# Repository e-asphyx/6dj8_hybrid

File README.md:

# DC coupled hybrid headphone amplifier
The input stage was inspired by Cavalli’s SOHA-II, but I have choose different output design. I use source follower loaded to Norton level shifter fed by op amp DC servo (inspired by TI’s LME49600 reference design) via current mirror to drive simple MOSFET source follower with SSC.

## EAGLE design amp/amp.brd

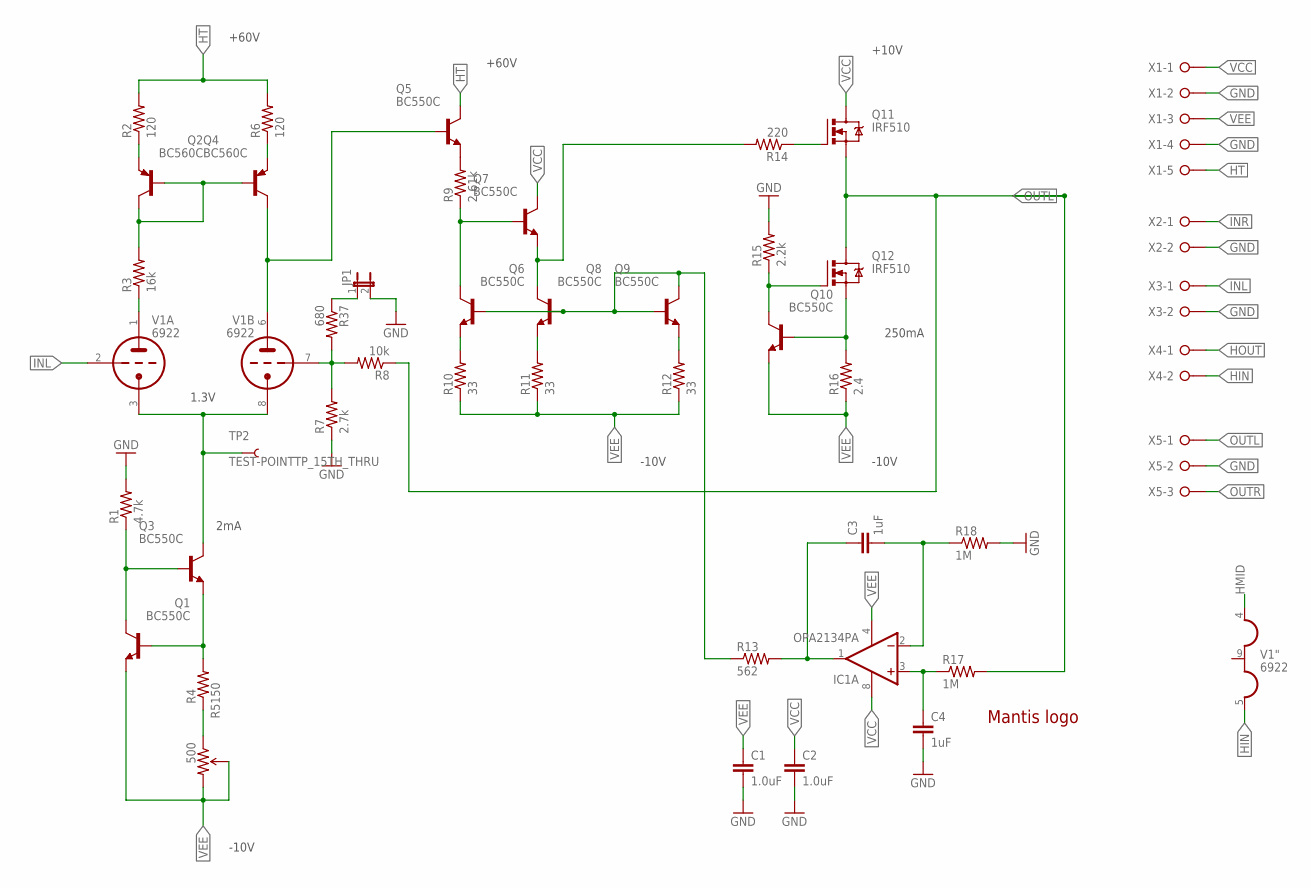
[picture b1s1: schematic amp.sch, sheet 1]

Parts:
C1, C2: 1.0uF; 0805-CAP
C3, C4: 1uF; C5B5
IC1: OPA2134PA; DIL08
JP1: JUMPER-2PTH; 1X02
LOGO1: LOGO-MANTIS
Q1, Q3, Q5, Q6, Q7, Q8, Q9, Q10: BC550C; TO92
Q2, Q4: BC560C; TO92-BENT
Q11, Q12: IRF510; TO220BV
R1: 4.7k; AXIAL-0.4
R2, R6: 120; AXIAL-0.4
R3: 16k; AXIAL-0.4
R4: 150; AXIAL-0.4
R5: 500; 3362U-2
R7: 2.7k; AXIAL-0.4
R8: 10k; AXIAL-0.4
R9: 2.61k; AXIAL-0.4
R10, R11, R12: 33; AXIAL-0.4
R13: 562; AXIAL-0.4
R14: 220; AXIAL-0.4
R15: 2.2k; AXIAL-0.4
R16: 2.4; AXIAL-0.5
R17, R18: 1M; AXIAL-0.4
R37: 680; AXIAL-0.4
TP2: TEST-POINTTP_15TH_THRU; TP_15TH
V1: 6922; NOVAL
X1: W237-05P; W237-5P
X2, X3, X4: W237-02P; W237-132
X5: W237-3E

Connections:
GND: C1.2, C2.2, C4.2, JP1.2, R1.P$2 (2), R7.P$1 (1), R15.P$2 (2), R18.P$2 (2), X1.2, X1.4, X2.2, X3.2, X5.2; also elsewhere on the board
HIN: V1.5 (H3), X4.2
HMID: V1.4 (H1); also elsewhere on the board
HOUT: X4.1; also elsewhere on the board
HT: Q5.3 (C), R2.P$2 (2), R6.P$2 (2), X1.5; also elsewhere on the board
INL: V1.2 (TG), X3.1
INR: X2.1; also elsewhere on the board
unnamed: Q3.3 (C), TP2.P$1, V1.3 (TK), V1.8 (TK)
unnamed: Q2.1 (C), Q2.2 (B), Q4.2 (B), R3.P$2 (2)
unnamed: Q2.3 (E), R2.P$1 (1)
unnamed: Q4.1 (C), Q5.2 (B), V1.6 (TA)
unnamed: R3.P$1 (1), V1.1 (TA)
unnamed: Q4.3 (E), R6.P$1 (1)
unnamed: Q1.2 (B), Q3.1 (E), R4.P$2 (2)
unnamed: Q1.3 (C), Q3.2 (B), R1.P$1 (1)
unnamed: R7.P$2 (2), R8.P$2 (2), R37.P$2 (2), V1.7 (TG)
unnamed: Q6.2 (B), Q8.2 (B), Q9.2 (B), Q9.3 (C), R13.P$1 (1)
unnamed: Q6.1 (E), R10.P$2 (2)
unnamed: Q9.1 (E), R12.P$2 (2)
unnamed: Q5.1 (E), R9.P$2 (2)
unnamed: Q10.3 (C), Q12.G, R15.P$1 (1)
unnamed: Q10.2 (B), Q12.S, R16.P$2 (2)
unnamed: C3.2, IC1.2 (-IN), R18.P$1 (1)
unnamed: C4.1, IC1.3 (+IN), R17.P$1 (1)
unnamed: C3.1, IC1.1 (OUT), R13.P$2 (2)
unnamed: Q8.1 (E), R11.P$2 (2)
unnamed: R4.P$1 (1), R5.1 (CCW)
unnamed: Q11.G, R14.P$1 (1)
unnamed: Q6.3 (C), Q7.2 (B), R9.P$1 (1)
unnamed: Q7.1 (E), Q8.3 (C), R14.P$2 (2)
unnamed: JP1.1, R37.P$1 (1)
OUTL: Q11.S, Q12.D, R8.P$1 (1), R17.P$2 (2), X5.1
OUTR: X5.3; also elsewhere on the board
VCC: C2.1, IC1.8 (V+), Q7.3 (C), Q11.D, X1.1; also elsewhere on the board
VEE: C1.1, IC1.4 (V-), Q1.1 (E), Q10.1 (E), R5.2 (WIPER), R5.3 (CW), R10.P$1 (1), R11.P$1 (1), R12.P$1 (1), R16.P$1 (1), X1.3; also elsewhere on the board

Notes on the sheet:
2mA
250mA
1.3V
+60V
+10V
-10V

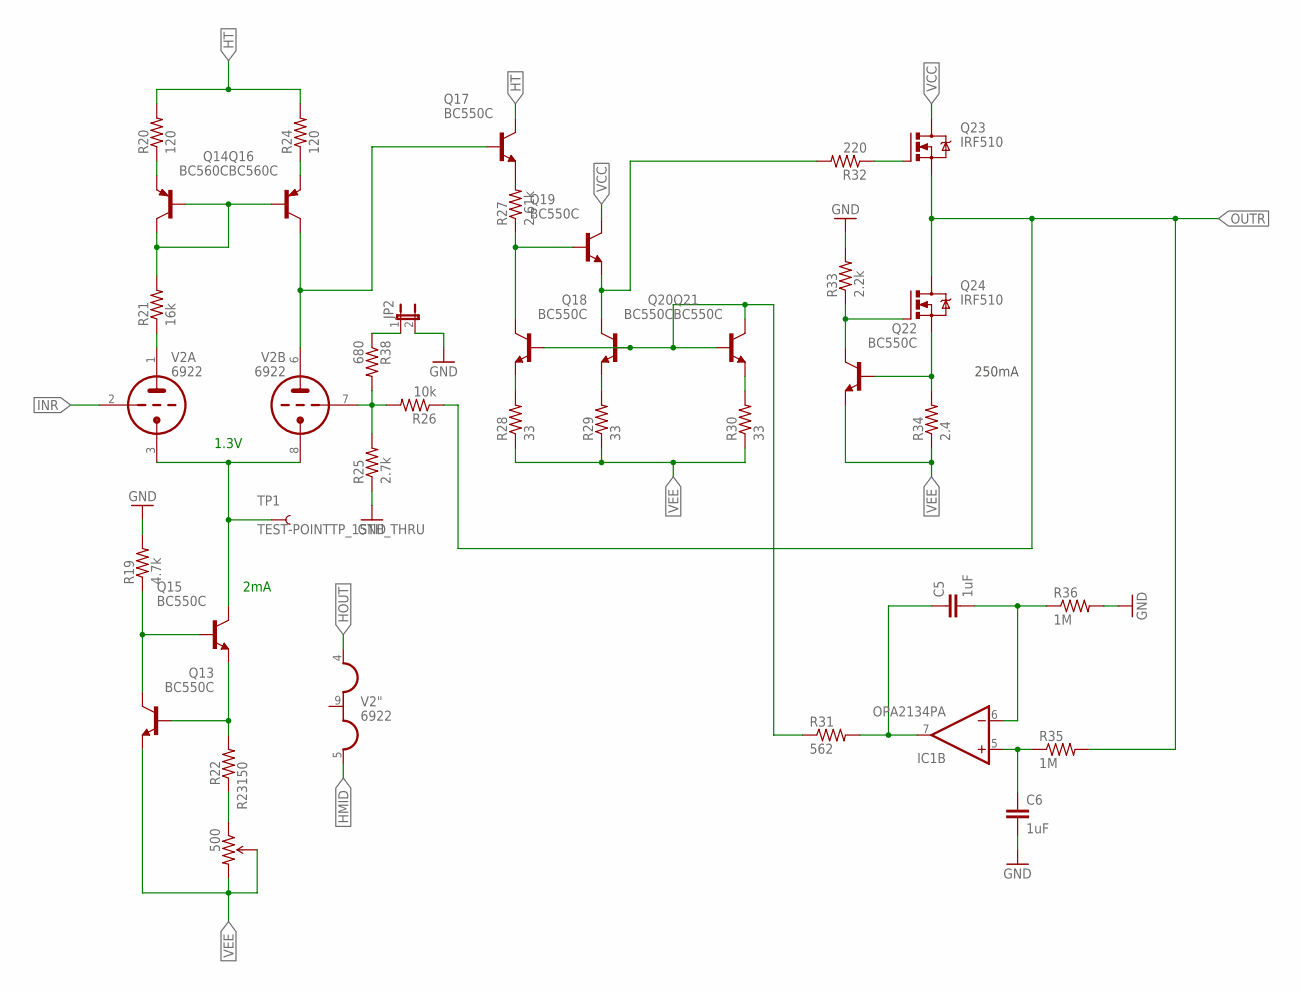
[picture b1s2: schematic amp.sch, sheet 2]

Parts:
C5, C6: 1uF; C5B5
IC1: OPA2134PA; DIL08
JP2: JUMPER-2PTH; 1X02
Q13, Q15, Q17, Q18, Q19, Q20, Q21, Q22: BC550C; TO92
Q14, Q16: BC560C; TO92-BENT
Q23, Q24: IRF510; TO220BV
R19: 4.7k; AXIAL-0.4
R20, R24: 120; AXIAL-0.4
R21: 16k; AXIAL-0.4
R22: 150; AXIAL-0.4
R23: 500; 3362U-2
R25: 2.7k; AXIAL-0.4
R26: 10k; AXIAL-0.4
R27: 2.61k; AXIAL-0.4
R28, R29, R30: 33; AXIAL-0.4
R31: 562; AXIAL-0.4
R32: 220; AXIAL-0.4
R33: 2.2k; AXIAL-0.4
R34: 2.4; AXIAL-0.5
R35, R36: 1M; AXIAL-0.4
R38: 680; AXIAL-0.4
TP1: TEST-POINTTP_15TH_THRU; TP_15TH
V2: 6922; NOVAL

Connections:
GND: C6.2, JP2.2, R19.P$2 (2), R25.P$1 (1), R33.P$2 (2), R36.P$2 (2); also elsewhere on the board
HMID: V2.5 (H3); also elsewhere on the board
HOUT: V2.4 (H1); also elsewhere on the board
HT: Q17.3 (C), R20.P$2 (2), R24.P$2 (2); also elsewhere on the board
INR: V2.2 (TG); also elsewhere on the board
unnamed: Q18.3 (C), Q19.2 (B), R27.P$1 (1)
unnamed: Q15.3 (C), TP1.P$1, V2.3 (TK), V2.8 (TK)
unnamed: Q14.1 (C), Q14.2 (B), Q16.2 (B), R21.P$2 (2)
unnamed: Q16.1 (C), Q17.2 (B), V2.6 (TA)
unnamed: R21.P$1 (1), V2.1 (TA)
unnamed: Q14.3 (E), R20.P$1 (1)
unnamed: Q16.3 (E), R24.P$1 (1)
unnamed: Q13.2 (B), Q15.1 (E), R22.P$2 (2)
unnamed: Q13.3 (C), Q15.2 (B), R19.P$1 (1)
unnamed: Q18.2 (B), Q20.2 (B), Q21.2 (B), Q21.3 (C), R31.P$1 (1)
unnamed: Q18.1 (E), R28.P$2 (2)
unnamed: Q21.1 (E), R30.P$2 (2)
unnamed: Q19.1 (E), Q20.3 (C), R32.P$2 (2)
unnamed: Q22.3 (C), Q24.G, R33.P$1 (1)
unnamed: Q22.2 (B), Q24.S, R34.P$2 (2)
unnamed: R25.P$2 (2), R26.P$2 (2), R38.P$2 (2), V2.7 (TG)
unnamed: C5.2, IC1.6 (-IN), R36.P$1 (1)
unnamed: C6.1, IC1.5 (+IN), R35.P$1 (1)
unnamed: C5.1, IC1.7 (OUT), R31.P$2 (2)
unnamed: R22.P$1 (1), R23.1 (CCW)
unnamed: Q23.G, R32.P$1 (1)
unnamed: Q17.1 (E), R27.P$2 (2)
unnamed: Q20.1 (E), R29.P$2 (2)
unnamed: JP2.1, R38.P$1 (1)
OUTR: Q23.S, Q24.D, R26.P$1 (1), R35.P$2 (2); also elsewhere on the board
VCC: Q19.3 (C), Q23.D; also elsewhere on the board
VEE: Q13.1 (E), Q22.1 (E), R23.2 (WIPER), R23.3 (CW), R28.P$1 (1), R29.P$1 (1), R30.P$1 (1), R34.P$1 (1); also elsewhere on the board

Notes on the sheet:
2mA
250mA
1.3V

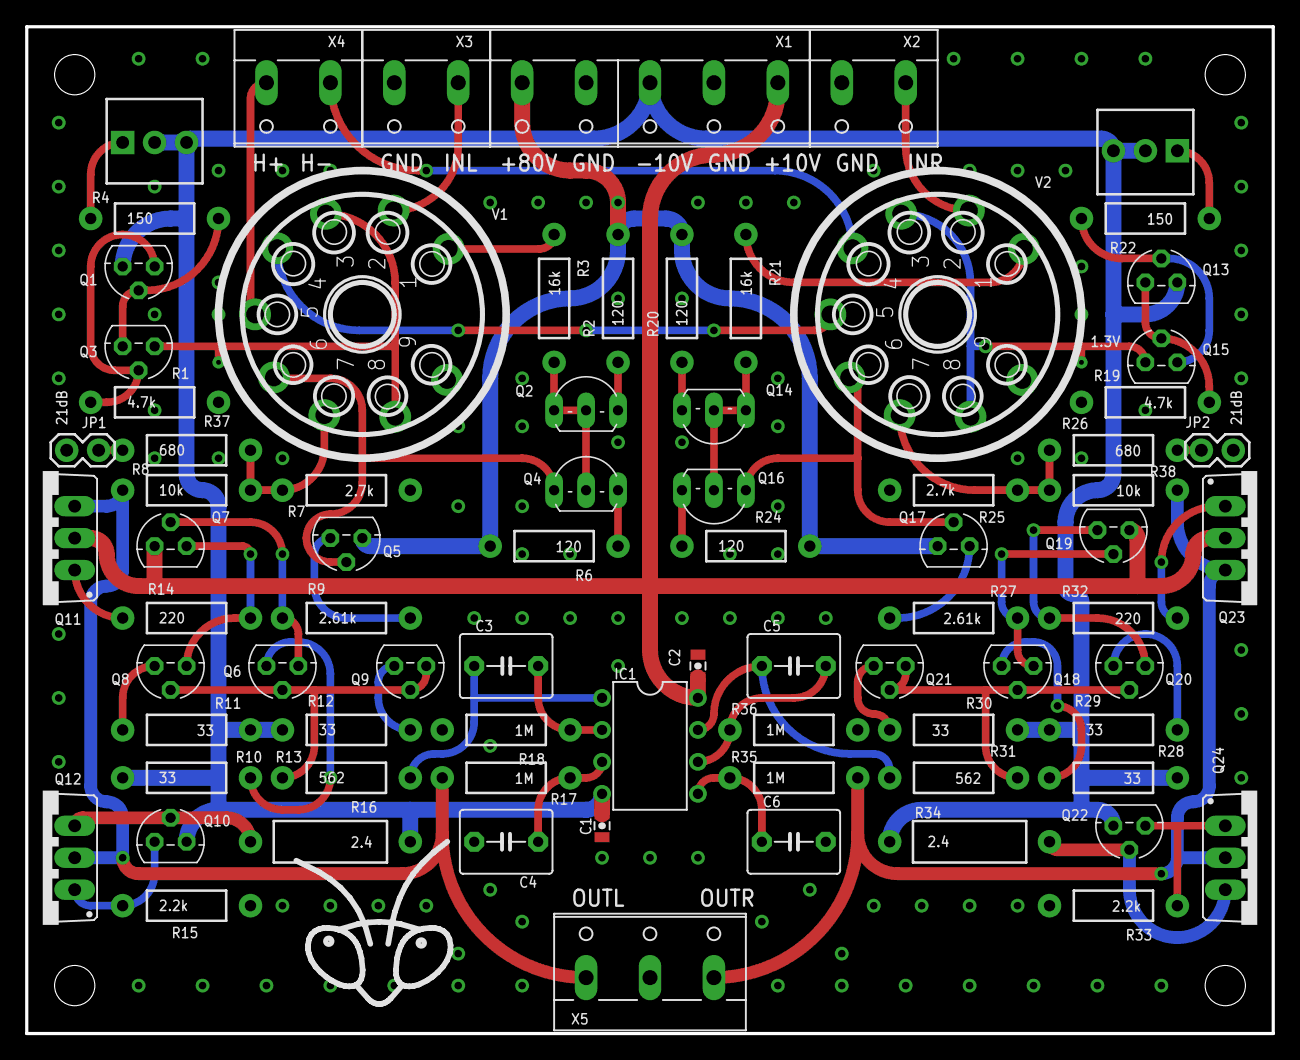
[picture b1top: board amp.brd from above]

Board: 2 copper layers, 99.1 x 80.0 mm, 81 parts (0 on the bottom side), 59 nets.

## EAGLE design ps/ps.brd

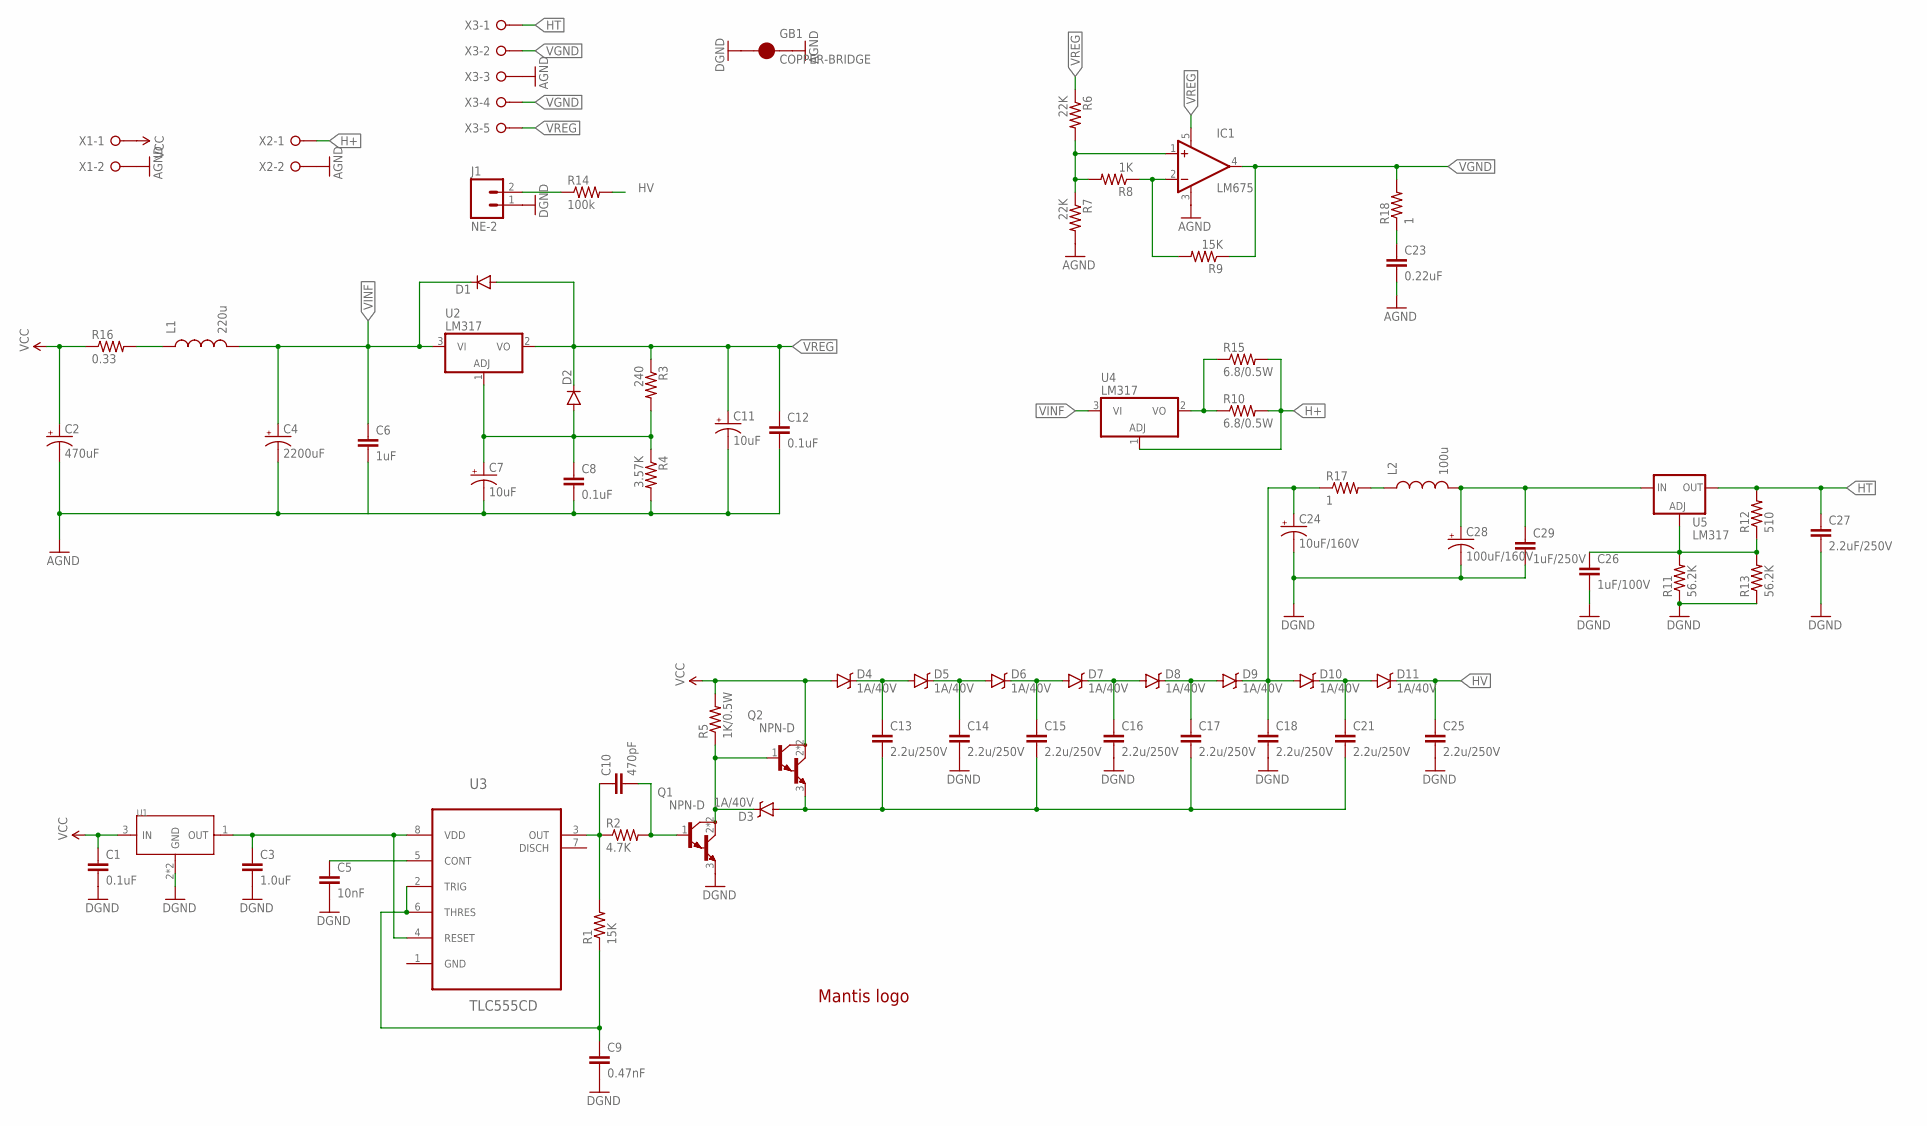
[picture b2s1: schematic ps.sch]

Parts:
C1, C8, C12: 0.1uF; 0603-CAP
C2: 470uF; CPOL-RADIAL-1000UF-25V
C3: 1.0uF; 0805-CAP
C4: 2200uF; CPOL-RADIAL-1000UF-63V
C5: 10nF; 0603-CAP
C6: 1uF; 0805-CAP
C7, C11: 10uF; PANASONIC_C
C9: 0.47nF; 0603-CAP
C10: 470pF; 0603-CAP
C13, C14, C15, C16, C17, C18, C21, C25: 2.2u/250V; C2220K
C23: 0.22uF; 0603-CAP
C24: 10uF/160V; CPOL-RADIAL-1000UF-25V
C26: 1uF/100V; 1210
C27: 2.2uF/250V; C2220K
C28: 100uF/160V; CPOL-RADIAL-1000UF-25V
C29: 1uF/250V; C2220K
D1, D2: DIODESOD123; SOD-123
D3, D4, D5, D6, D7, D8, D9, D10, D11: 1A/40V; SMA-DIODE
GB1: COPPER-BRIDGE
IC1: LM675; TO220-5
J1: NE-2; 1X02
L1: 220u; NR10050T-PTH-ADD
L2: 100u; 1210; MOUSER_PRICE 0.168
LOGO1: LOGO-MANTIS
Q1, Q2: NPN-D; SOT223
R1: 15K; 0603-RES
R2: 4.7K; 0603-RES
R3: 240; AXIAL-0.4
R4: 3.57K; AXIAL-0.4
R5: 1K/0.5W; R1210W
R6, R7: 22K; AXIAL-0.4
R8: 1K; AXIAL-0.4
R9: 15K; AXIAL-0.4
R10, R15: 6.8/0.5W; AXIAL-0.5
R11, R13: 56.2K; AXIAL-0.4
R12: 510; AXIAL-0.4
R14: 100k; 0603-RES
R16: 0.33; AXIAL-0.4
R17: 1; AXIAL-0.1
R18: 1; AXIAL-0.4
U1: L78L12ACUTR; SOT-89
U2, U4: LM317; TO220BV
U3: TLC555CD; SOIC127P600X175-8N
U5: LM317; V-REG_DPACK
X1, X2: W237-02P; W237-132
X3: W237-05P; W237-5P

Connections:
555CONT: C5.1, U3.5 (CONT)
555OUT: C10.1, R1.2, R2.1, U3.3 (OUT)
555TRIG: C9.1, R1.1, U3.2 (TRIG), U3.6 (THRES)
555VDD: C3.1, U1.1 (OUT), U3.4 (RESET), U3.8 (VDD)
AGND: C2.-, C4.2 (-), C6.2, C7.-, C8.2, C11.-, C12.2, C23.2, GB1.P$2.1 (2), GB1.P$2.2 (2), IC1.3 (V-), R4.P$2 (2), R7.P$2 (2), X1.2, X2.2, X3.3
GND: C1.2, C3.2, C5.2, C9.2, C14.2, C16.2, C18.2, C24.-, C25.2, C26.2, C27.2, C28.-, C29.2, GB1.P$1.1 (1), GB1.P$1.2 (1), J1.1, Q1.3 (E), R11.P$1 (1), R13.P$1 (1), U1.2 (GND), U1.PAD (GND)
H+: R10.P$2 (2), R15.P$2 (2), U4.1 (ADJ), X2.1
HT: C27.1, R12.P$2 (2), U5.4 (OUT), X3.1
HV: C25.1, D11.C, R14.2
unnamed: D3.C, Q1.2 (C), Q1.4 (C), Q2.1 (B), R5.1
unnamed: IC1.1 (+IN), R6.P$2 (2), R7.P$1 (1), R8.P$2 (2)
unnamed: IC1.2 (-IN), R8.P$1 (1), R9.P$2 (2)
unnamed: C21.1, D10.C, D11.A
unnamed: J1.2, R14.1
unnamed: C13.1, D4.C, D5.A
unnamed: C28.+, C29.1, L2.2, U5.3 (IN)
unnamed: R10.P$1 (1), R15.P$1 (1), U4.2 (VO)
unnamed: L1.P$1 (1), L1.P$1.1 (1), R16.P$2 (2)
unnamed: C10.2, Q1.1 (B), R2.2
unnamed: C14.1, D5.C, D6.A
unnamed: C15.1, D6.C, D7.A
unnamed: C16.1, D7.C, D8.A
unnamed: C17.1, D8.C, D9.A
unnamed: C18.1, C24.+, D9.C, D10.A, R17.P$1 (1)
unnamed: L2.1, R17.P$2 (2)
unnamed: C23.1, R18.P$1 (1)
unnamed: C26.1, R11.P$2 (2), R12.P$1 (1), R13.P$2 (2), U5.1 (ADJ)
PUMPIN: C13.2, C15.2, C17.2, C21.2, D3.A, Q2.3 (E)
REGADJ: C7.+, C8.1, D2.A, R3.P$2 (2), R4.P$1 (1), U2.1 (ADJ)
VCC: C1.1, C2.+, D4.A, Q2.2 (C), Q2.4 (C), R5.2, R16.P$1 (1), U1.3 (IN), X1.1
VGND: IC1.4 (OUT), R9.P$1 (1), R18.P$2 (2), X3.2, X3.4
VINF: C4.1 (+), C6.1, D1.C, L1.P$2 (2), L1.P$2.1 (2), U2.3 (VI), U4.3 (VI)
VREG: C11.+, C12.1, D1.A, D2.C, IC1.5 (V+), R3.P$1 (1), R6.P$1 (1), U2.2 (VO), X3.5

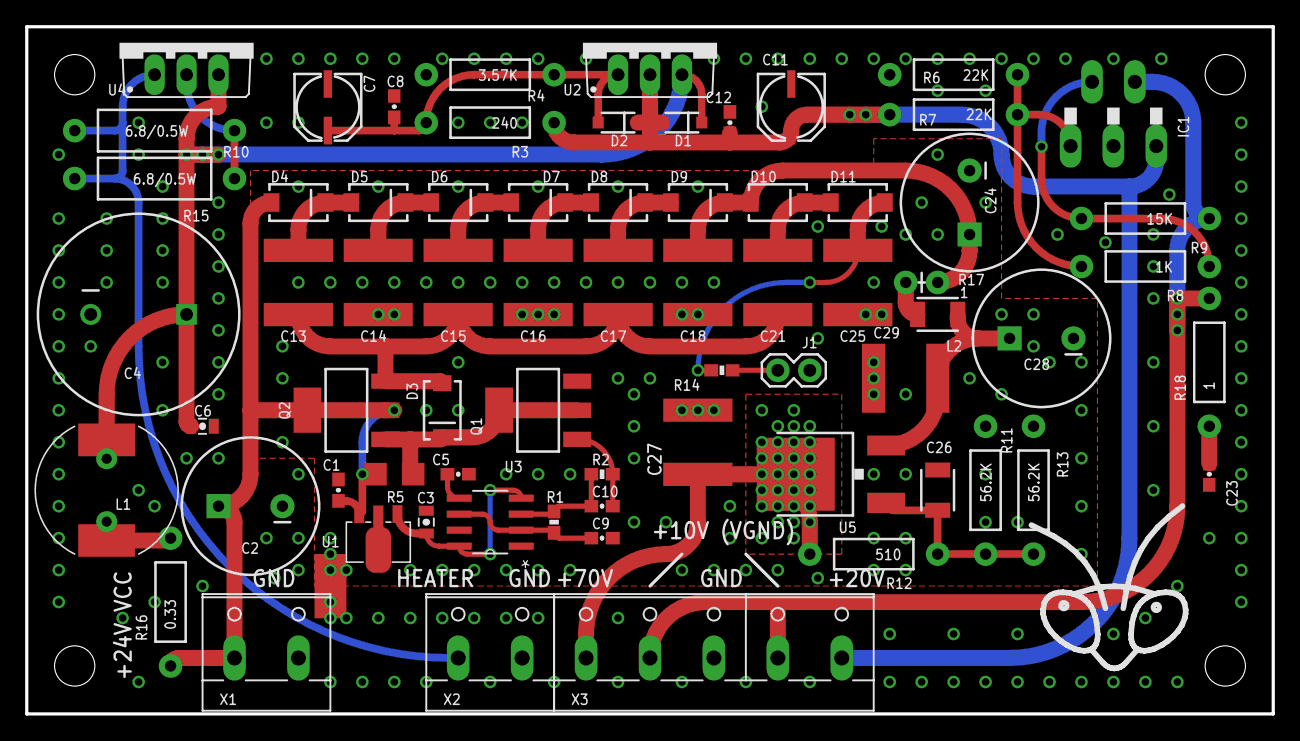
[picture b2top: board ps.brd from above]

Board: 2 copper layers, 99.1 x 54.6 mm, 71 parts (0 on the bottom side), 33 nets.

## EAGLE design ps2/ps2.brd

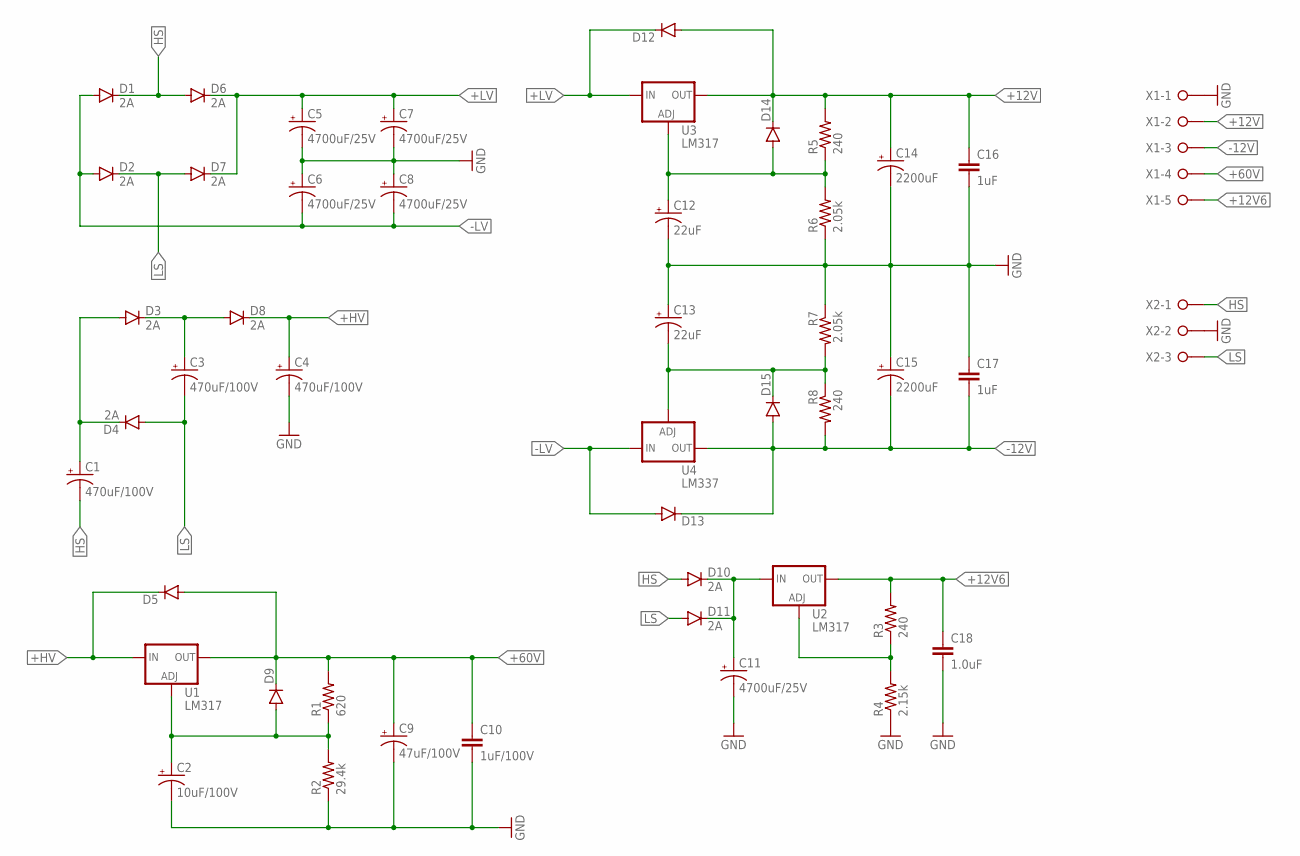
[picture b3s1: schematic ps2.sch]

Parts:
C1, C3, C4: 470uF/100V; CPOL-RADIAL-1000UF-63V
C2: 10uF/100V; CPOL-RADIAL-100UF-25V
C5, C6, C7, C8, C11: 4700uF/25V; CPOL-RADIAL-1000UF-63V
C9: 47uF/100V; CPOL-RADIAL-1000UF-25V
C10: 1uF/100V; C1206
C12, C13: 22uF; CPOL-RADIAL-10UF-25V
C14, C15: 2200uF; CPOL-RADIAL-1000UF-25V
C16, C17: 1uF; 0805-CAP
C18: 1.0uF; 0805-CAP
D1, D2, D3, D4, D6, D7, D8, D10, D11: 2A; SMA-DIODE
D5, D9, D12, D13, D14, D15: DIODESMA; SMA-DIODE
R1: 620; AXIAL-0.4
R2: 29.4k; AXIAL-0.4
R3, R5, R8: 240; AXIAL-0.4
R4: 2.15k; AXIAL-0.4
R6, R7: 2.05k; AXIAL-0.4
U1, U2, U3: LM317; V-REG_DPACK
U4: LM337; V-REG_DPACK
X1: W237-05P; W237-5P
X2: W237-3E

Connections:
+12V: C14.+, C16.1, D12.A, D14.C, R5.P$2 (2), U3.4 (OUT), X1.2
+12V6: C18.1, R3.P$2 (2), U2.4 (OUT), X1.5
+60V: C9.+, C10.1, D5.A, D9.C, R1.P$2 (2), U1.4 (OUT), X1.4
+HV: C4.1 (+), D5.C, D8.C, U1.3 (IN)
+LV: C5.1 (+), C7.1 (+), D6.C, D7.C, D12.C, U3.3 (IN)
-12V: C15.-, C17.2, D13.C, D15.A, R8.P$2 (2), U4.3 (OUT), X1.3
-LV: C6.2 (-), C8.2 (-), D1.A, D2.A, D13.A, U4.2 (IN)
GND: C2.2 (-), C4.2 (-), C5.2 (-), C6.1 (+), C7.2 (-), C8.1 (+), C9.-, C10.2, C11.2 (-), C12.2 (-), C13.1 (+), C14.-, C15.+, C16.2, C17.1, C18.2, R2.P$1 (1), R4.P$1 (1), R6.P$1 (1), R7.P$1 (1), X1.1, X2.2
HS: C1.2 (-), D1.C, D6.A, D10.A, X2.1
LS: C3.2 (-), D2.C, D4.A, D7.A, D11.A, X2.3
unnamed: C1.1 (+), D3.A, D4.C
unnamed: C3.1 (+), D3.C, D8.A
unnamed: C13.2 (-), D15.C, R7.P$2 (2), R8.P$1 (1), U4.1 (ADJ)
unnamed: C12.1 (+), D14.A, R5.P$1 (1), R6.P$2 (2), U3.1 (ADJ)
unnamed: C2.1 (+), D9.A, R1.P$1 (1), R2.P$2 (2), U1.1 (ADJ)
unnamed: R3.P$1 (1), R4.P$2 (2), U2.1 (ADJ)
unnamed: C11.1 (+), D10.C, D11.C, U2.3 (IN)

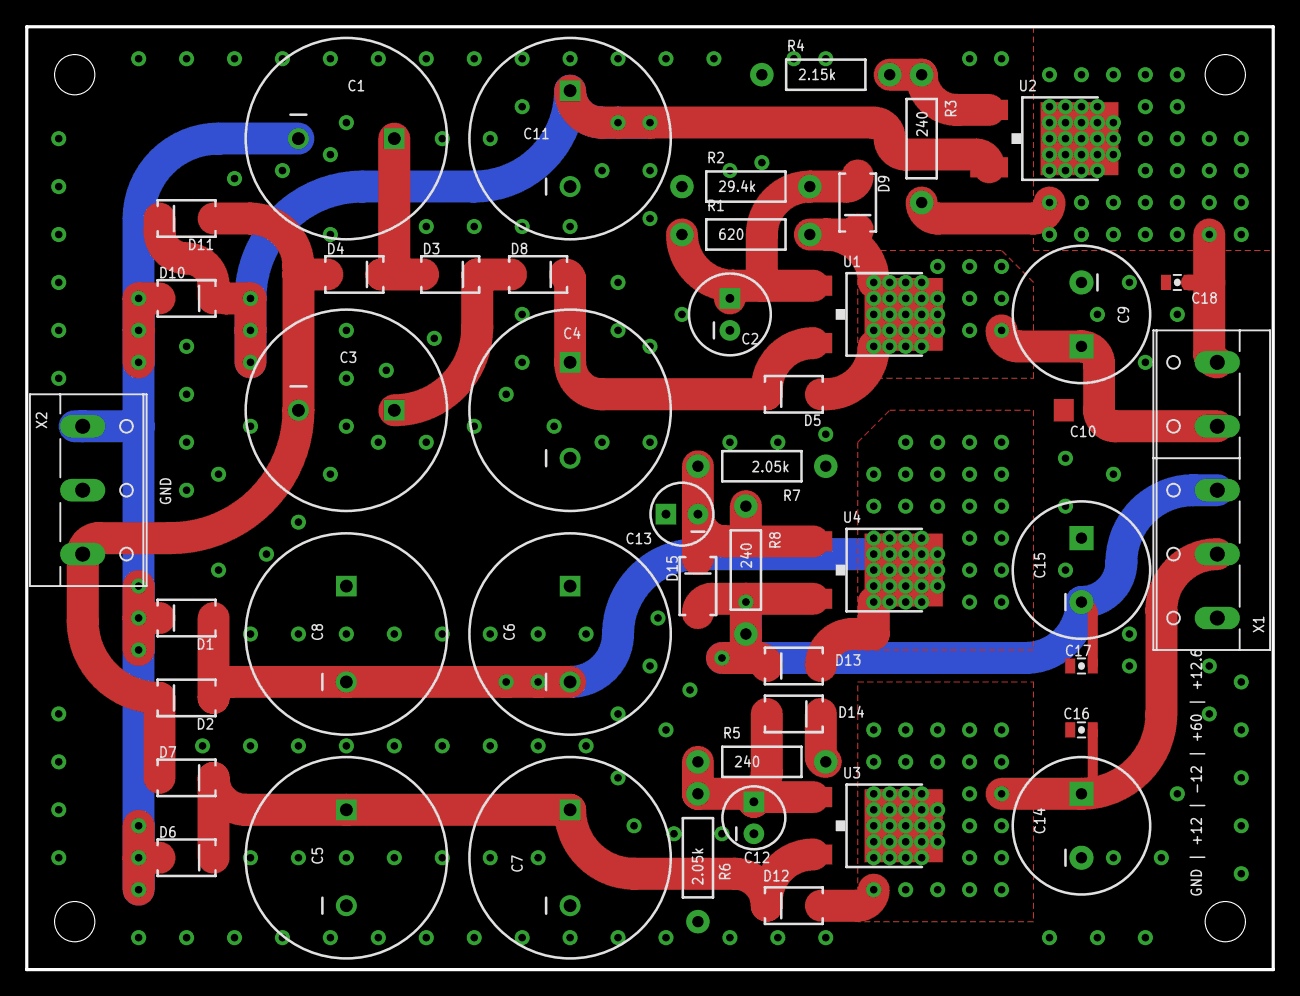
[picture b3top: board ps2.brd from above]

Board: 2 copper layers, 99.1 x 74.9 mm, 47 parts (0 on the bottom side), 17 nets.

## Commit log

2016-08-27 Missed PDFs
2016-09-02 Back to 60V supply
2016-09-06 HV for neon bulb
2016-09-06 Some tweaks
2016-09-09 PSU tweaked
2016-09-09 More filtering
2016-09-10 Gate resistors added
2016-09-10 Back to IRF5xx
2016-09-10 HT filter added
2016-09-10 Unneeded resistors
2016-09-10 PDFs updated
2016-09-11 PS rerouted
2016-09-11 Separated grounds
2016-09-12 More tweaks
2016-09-13 Small bypass cap added
2016-09-13 High frequency snubber
2016-09-15 MOSFET driver stage
2016-09-23 Gain switching jumper
2016-10-02 AC PSU done
2016-10-02 oops
2016-10-02 Small tweak
2016-10-03 LC damping resistors added to PS
2016-10-03 Unneeded caps removed
2016-10-03 PDFs
2016-10-08 CM degeneration values lowered
2016-10-16 Some components changed

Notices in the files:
parts and their libraries:
SparkFun-Resistors: Licensing: Creative Commons ShareAlike 4.0 International - https://creativecommons.org/licenses/by-sa/4.0
